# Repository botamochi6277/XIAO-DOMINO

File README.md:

# XIAO Expansion Board, DOMINO

_DOMINO_ is an extension board for [XIAO Series Boards of Seeed Studio](https://www.seeedstudio.com/xiao-series-page).

## Specifications

- Dimensions: 26 x 52
- Interface:
  - I2C Grove Connector
  - SPI Grove Connector
  - JST PH Power Connector
  - XIAO RAW PINS

## Note

original domino dimension is approx 25x50mm([wiki.ja](https://ja.wikipedia.org/wiki/ドミノ))

XIAO Power:

## Chips

- LED: M1608 (0603 inch)
- Resistor: M1608 (0603 inch)
- Capacitor: M3216 (1206 inch)

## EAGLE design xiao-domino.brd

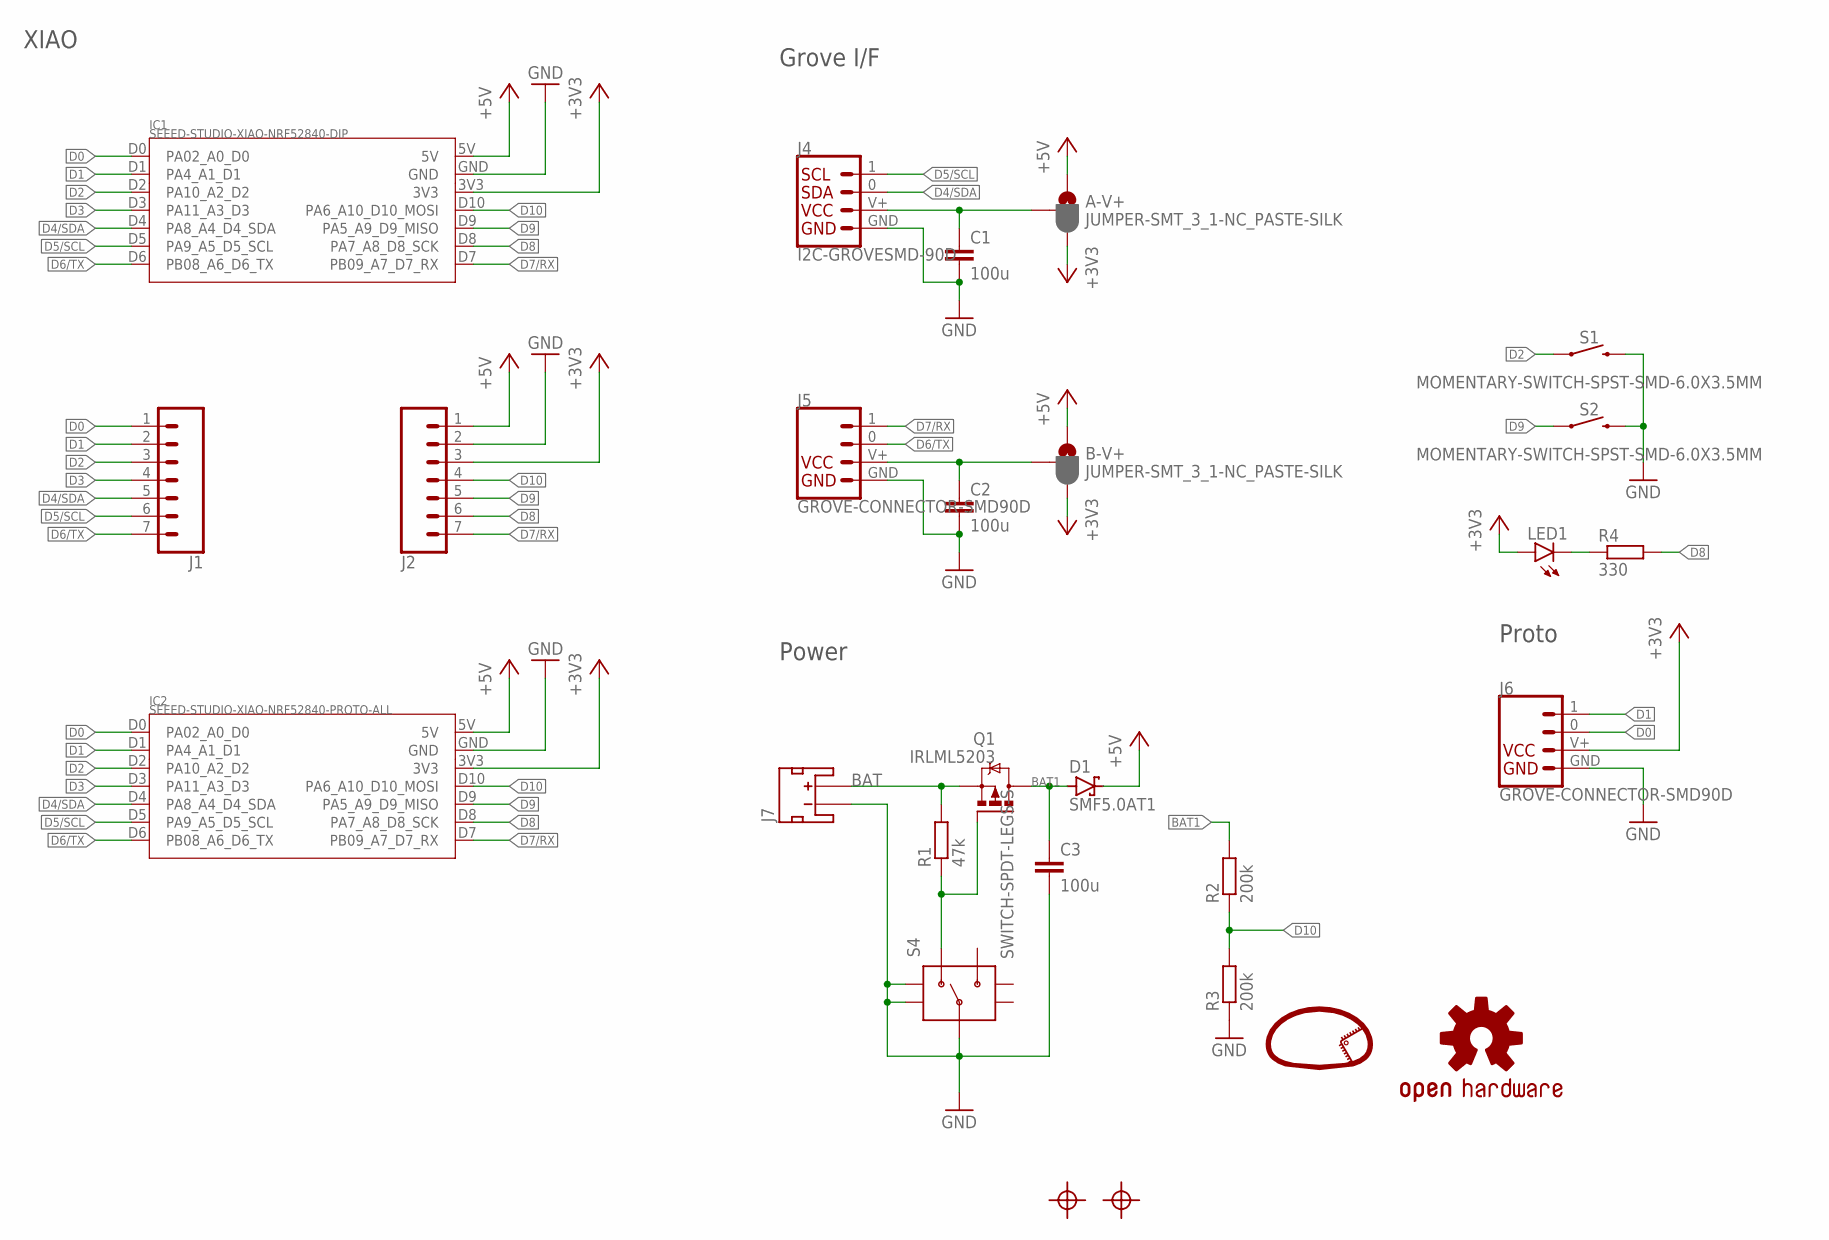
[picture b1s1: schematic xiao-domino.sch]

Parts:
A-V+: JUMPER-SMT_3_1-NC_PASTE-SILK; SMT-JUMPER_3_1-NC_PASTE_SILK
B-V+: JUMPER-SMT_3_1-NC_PASTE-SILK; SMT-JUMPER_3_1-NC_PASTE_SILK
C1, C2, C3: 100u; C3216
D1: SMF5.0AT1; SOD123FL
H1, H2: HOLE-SILK-2.1; MOUNTING_HOLE_SILK_2.1
IC1: SEEED-STUDIO-XIAO-NRF52840-DIP; XIAO-NRF52840-DIP
IC2: SEEED-STUDIO-XIAO-NRF52840-PROTO-ALL; XIAO-SMD-PROTO
J1, J2: CONN_07NO_SILK; 1X07_NO_SILK
J4: I2C-GROVESMD-90D; HW4-SMD-2.0-90D
J5, J6: GROVE-CONNECTOR-SMD90D; HW4-SMD-2.0-90D
J7: JST_2MM_MALE; JST-2-SMD
LED1: LEDCHIP-LED0603; CHIP-LED0603
LOGO1: LOGO
LOGO2: OSHW-LOGOS; OSHW-LOGO-S
Q1: IRLML5203; MICRO3
R1: 47k; R0603
R2, R3: 200k; R0603
R4: 330; R0603
S1, S2: MOMENTARY-SWITCH-SPST-SMD-6.0X3.5MM; TACTILE_SWITCH_SMD_6.0X3.5MM
S4: SWITCH-SPDT-LEGS-S; SWITCH_SPST_SMD_A

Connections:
+3V3: A-V+.3, B-V+.3, IC1.3V3, IC2.3V3, J2.3, J6.V+ (VCC), LED1.A
+5V: A-V+.1, B-V+.1, D1.C, IC1.5V, IC2.5V, J2.1
BAT: J7.2 (+), Q1.2 (S), R1.2
BAT1: C3.1, D1.A, Q1.3 (D), R2.2
D0: IC1.D0 (PA02_A0_D0), IC2.D0 (PA02_A0_D0), J1.1, J6.0 (3)
D1: IC1.D1 (PA4_A1_D1), IC2.D1 (PA4_A1_D1), J1.2, J6.1 (4)
D2: IC1.D2 (PA10_A2_D2), IC2.D2 (PA10_A2_D2), J1.3, S1.1
D3: IC1.D3 (PA11_A3_D3), IC2.D3 (PA11_A3_D3), J1.4
D4/SDA: IC1.D4 (PA8_A4_D4_SDA), IC2.D4 (PA8_A4_D4_SDA), J1.5, J4.0 (3)
D5/SCL: IC1.D5 (PA9_A5_D5_SCL), IC2.D5 (PA9_A5_D5_SCL), J1.6, J4.1 (4)
D6/TX: IC1.D6 (PB08_A6_D6_TX), IC2.D6 (PB08_A6_D6_TX), J1.7, J5.0 (3)
D7/RX: IC1.D7 (PB09_A7_D7_RX), IC2.D7 (PB09_A7_D7_RX), J2.7, J5.1 (4)
D8: IC1.D8 (PA7_A8_D8_SCK), IC2.D8 (PA7_A8_D8_SCK), J2.6, R4.2
D9: IC1.D9 (PA5_A9_D9_MISO), IC2.D9 (PA5_A9_D9_MISO), J2.5, S2.1
D10: IC1.D10 (PA6_A10_D10_MOSI), IC2.D10 (PA6_A10_D10_MOSI), J2.4, R2.1, R3.2
GND: C1.2, C2.2, C3.2, IC1.GND, IC2.GND, J2.2, J4.GND (1), J5.GND, J6.GND, J7.1 (-), R3.1, S1.2, S2.2, S4.2, S4.L$1, S4.L$2
unnamed: A-V+.2, C1.1, J4.V+ (2)
unnamed: B-V+.2, C2.1, J5.V+ (VCC)
unnamed: Q1.1 (G), R1.1, S4.1 (O)
unnamed: LED1.C, R4.1

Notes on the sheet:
Power
Grove I/F
XIAO
Proto

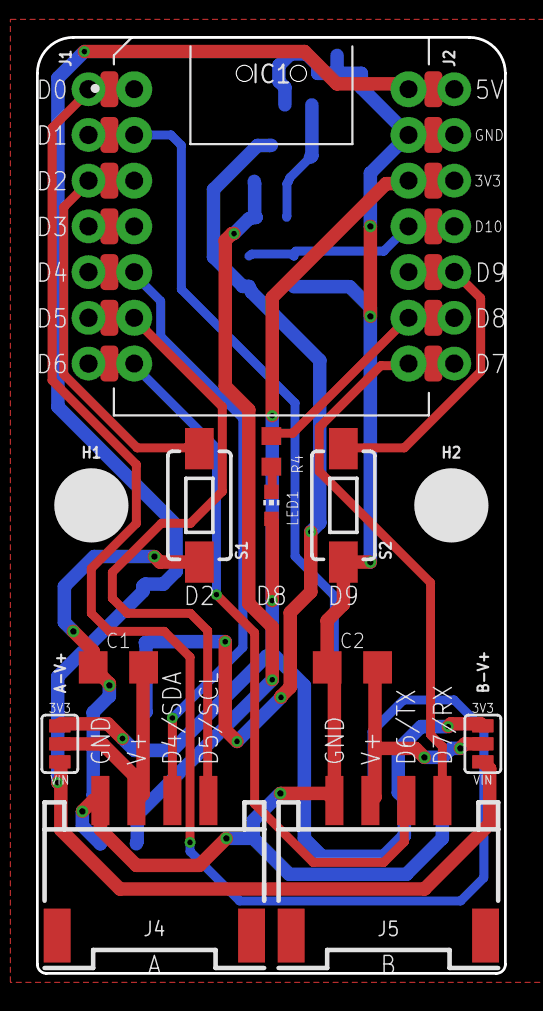
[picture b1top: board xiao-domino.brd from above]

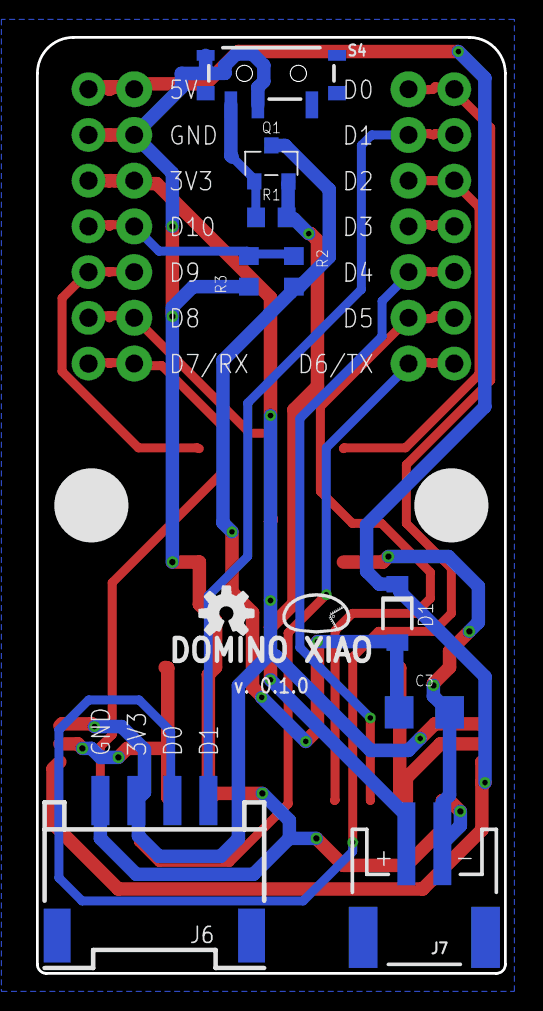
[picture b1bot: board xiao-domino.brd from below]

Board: 2 copper layers, 26.0 x 52.0 mm, 27 parts (11 on the bottom side), 20 nets.

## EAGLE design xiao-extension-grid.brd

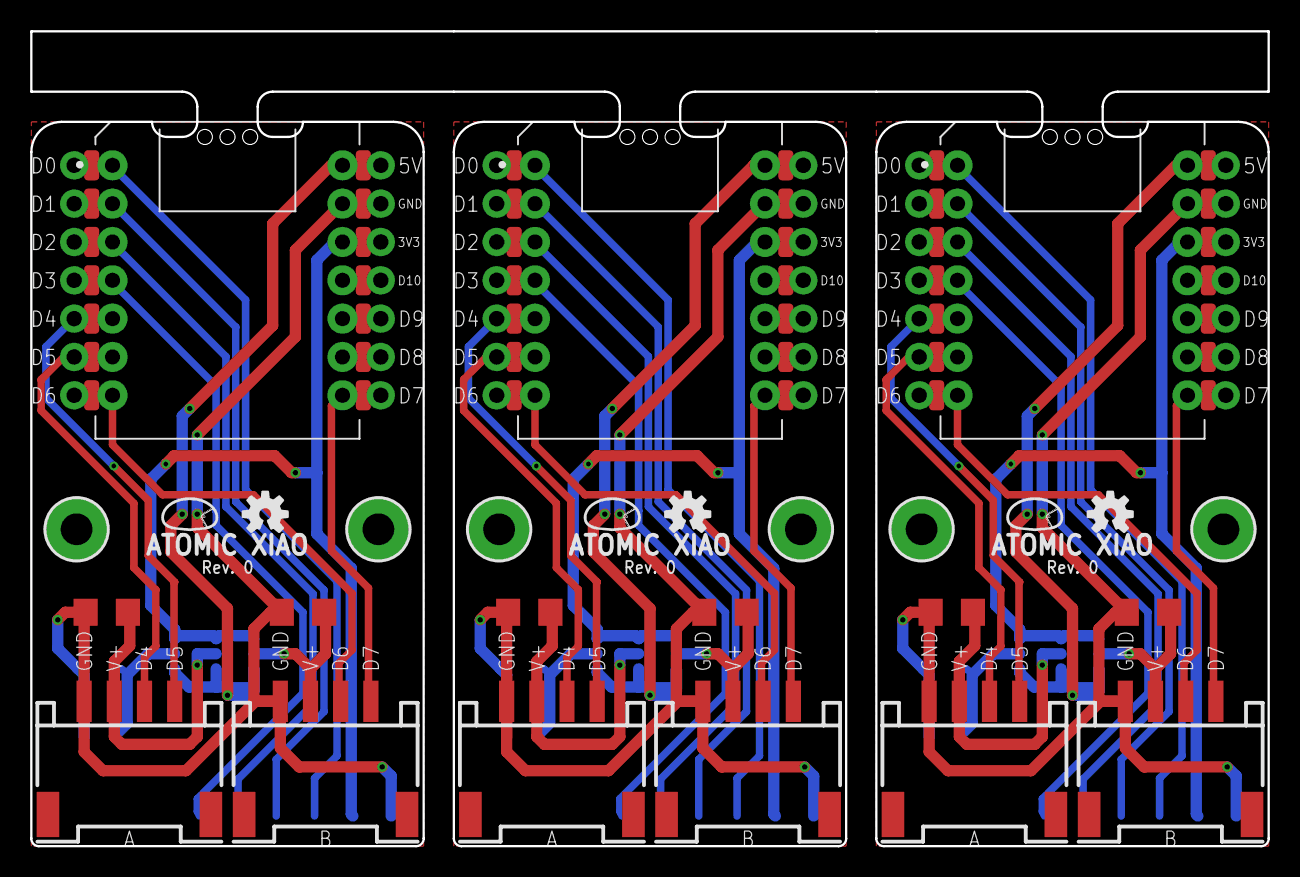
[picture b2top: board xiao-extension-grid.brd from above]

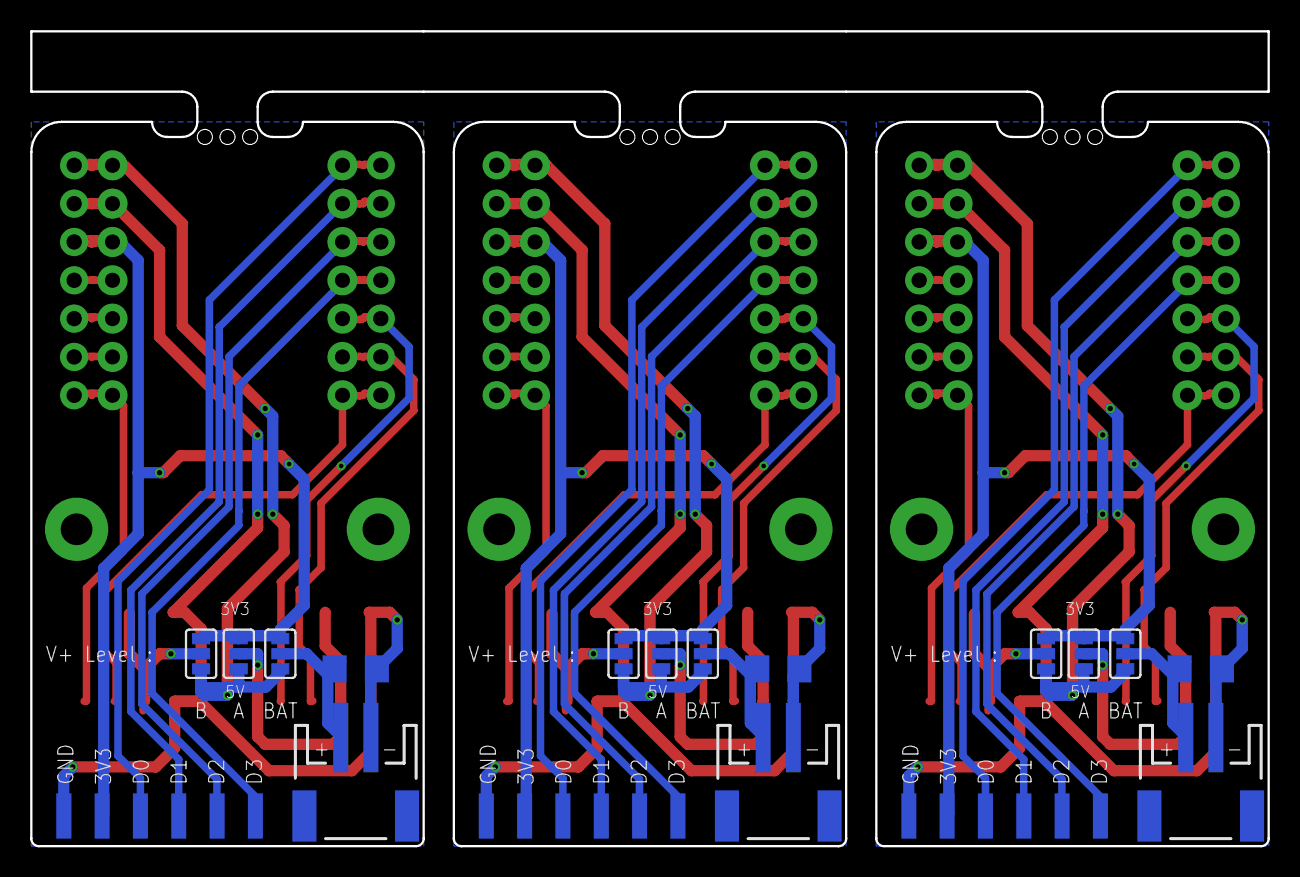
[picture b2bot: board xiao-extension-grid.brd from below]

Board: 2 copper layers, 82.0 x 54.0 mm, 54 parts (18 on the bottom side), 51 nets.

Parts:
C1, C2, C3, C4, C5, C6, C7, C8, C9: 100u; C3216
H1, H2, H3, H4, H5, H6: HOLE-2.1; MOUNTING_HOLE_2.1
IC1, IC3, IC5: SEEED-STUDIO-XIAO-NRF52840-DIP; XIAO-NRF52840-DIP
IC2, IC4, IC6: SEEED-STUDIO-XIAO-NRF52840-PROTO; XIAO-NRF52840-SMD-PROTO
J1, J2, J10, J11, J19, J20: 1X07_NO_SILK
J3, J12, J21: JST-2-SMD
J4, J5, J15, J16, J24, J25: GROVE-CONNECTOR-SMD90D; HW4-SMD-2.0-90D
J6, J7, J8, J13, J14, J17, J22, J23, J26: JUMPER-SMT_3_1-NC_PASTE-SILK; SMT-JUMPER_3_1-NC_PASTE_SILK
J9, J18, J27: RA 6Pin SMD; 1X06-SMD_RA_MALE
LOGO1, LOGO3, LOGO5: LOGO
LOGO2, LOGO4, LOGO6: OSHW-LOGOS; OSHW-LOGO-S

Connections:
+3V1: IC3.3V3, IC4.3V3, J11.3, J13.3, J14.3, J17.3, J18.2
+3V2: IC5.3V3, IC6.3V3, J20.3, J22.3, J23.3, J26.3, J27.2
+3V3: IC1.3V3, IC2.3V3, J2.3, J6.3, J7.3, J8.3, J9.2
+5V: IC1.5V, IC2.5V, J2.1, J6.1, J7.1, J8.1
+5V1: IC3.5V, IC4.5V, J11.1, J13.1, J14.1, J17.1
+5V2: IC5.5V, IC6.5V, J20.1, J22.1, J23.1, J26.1
D0: IC1.D0, IC2.D0, J1.1, J9.3
D1: IC1.D1, IC2.D1, J1.2, J9.4
D2: IC1.D2, IC2.D2, J1.3, J9.5
D3: IC1.D3, IC2.D3, J1.4, J9.6
D4: IC3.D0, IC4.D0, J10.1, J18.3
D5: IC3.D1, IC4.D1, J10.2, J18.4
D6: IC3.D2, IC4.D2, J10.3, J18.5
D7: IC3.D3, IC4.D3, J10.4, J18.6
D8: IC1.D9, IC2.D9, J2.5
D9: IC1.D8, IC2.D8, J2.6
D10: IC1.D10, IC2.D10, J2.4
D11: IC3.D10, IC4.D10, J11.4
D12: IC3.D9, IC4.D9, J11.5
D13: IC3.D8, IC4.D8, J11.6
D14: IC5.D0, IC6.D0, J19.1, J27.3
D15: IC5.D1, IC6.D1, J19.2, J27.4
D16: IC5.D2, IC6.D2, J19.3, J27.5
D17: IC5.D3, IC6.D3, J19.4, J27.6
D18: IC5.D10, IC6.D10, J20.4
D19: IC5.D9, IC6.D9, J20.5
D20: IC5.D8, IC6.D8, J20.6
GND: C1.2, C2.2, C3.2, IC1.GND, IC2.GND, J2.2, J3.1, J4.GND, J5.GND, J9.1
GND1: C4.2, C5.2, C6.2, IC3.GND, IC4.GND, J11.2, J12.1, J15.GND, J16.GND, J18.1
GND2: C7.2, C8.2, C9.2, IC5.GND, IC6.GND, J20.2, J21.1, J24.GND, J25.GND, J27.1
unnamed: C1.1, J4.V+, J6.2
unnamed: C2.1, J5.V+, J7.2
unnamed: C3.1, J3.2, J8.2
unnamed: C4.1, J13.2, J16.V+
unnamed: C5.1, J14.2, J15.V+
unnamed: C6.1, J12.2, J17.2
unnamed: C7.1, J22.2, J25.V+
unnamed: C8.1, J23.2, J24.V+
unnamed: C9.1, J21.2, J26.2
RX: IC1.D7, IC2.D7, J2.7, J5.1
RX1: IC3.D7, IC4.D7, J11.7, J15.1
RX2: IC5.D7, IC6.D7, J20.7, J24.1
SCL: IC1.D5, IC2.D5, J1.6, J4.0
SCL1: IC3.D5, IC4.D5, J10.6, J16.0
SCL2: IC5.D5, IC6.D5, J19.6, J25.0
SDA: IC1.D4, IC2.D4, J1.5, J4.1
SDA1: IC3.D4, IC4.D4, J10.5, J16.1
SDA2: IC5.D4, IC6.D4, J19.5, J25.1
TX: IC1.D6, IC2.D6, J1.7, J5.0
TX1: IC3.D6, IC4.D6, J10.7, J15.0
TX2: IC5.D6, IC6.D6, J19.7, J24.0

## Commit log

2023-03-20 complete placing
2023-06-28 rename
2023-06-28 add image
2023-06-28 remove old penalized design

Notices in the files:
parts and their libraries:
SparkFun-Aesthetics: Licensing: Creative Commons ShareAlike 4.0 International - https://creativecommons.org/licenses/by-sa/4.0
